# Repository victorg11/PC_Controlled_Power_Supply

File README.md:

# PC_Controlled_Power_Supply

This repository contains important information regarding the PC controlled power supply assembled in Spring 2018. This project was completed on a three month timeline with two additional team members.

Project features:
- Can supply voltages ranging 2 to 14 V.
- Capable of withstanding loads up to 1.5 A.
- Voltages and currents are adjustable via mounted buttons on encasing and USB serial connection using the standard SCPI instrumentation protocol.
- Sampled voltages and currents are displayed on an LCD touchscreen display using the SPI protocol.
- Capable of disabling outputs once maximum desired load is reached.

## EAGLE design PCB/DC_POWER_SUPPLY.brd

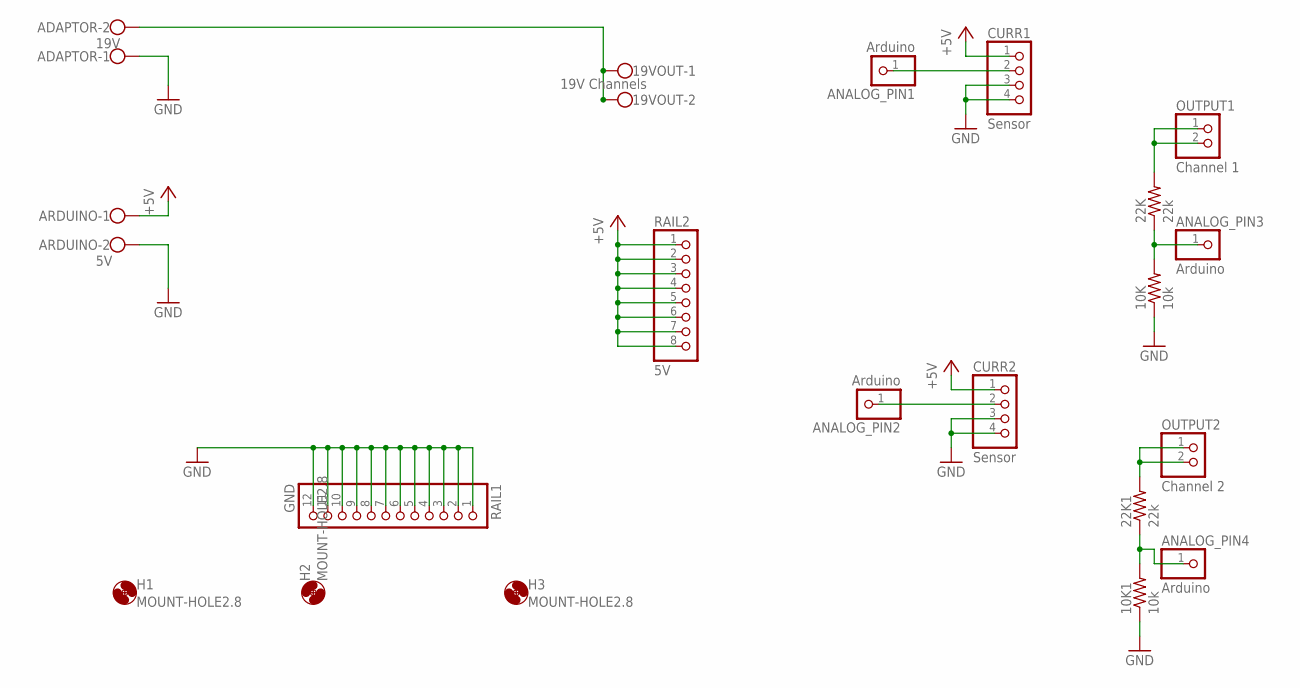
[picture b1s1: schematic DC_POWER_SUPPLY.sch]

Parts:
10K, 10K1: 10k; 0204/7
19VOUT: 19V Channels; W237-102
22K: 22k; 0207/7
22K1: 22k; 0204/7
ADAPTOR: 19V; W237-102
ANALOG_PIN1, ANALOG_PIN2, ANALOG_PIN3, ANALOG_PIN4: Arduino; 1X01
ARDUINO: 5V; W237-102
CURR1, CURR2: Sensor; 1X04
H1, H2, H3: MOUNT-HOLE2.8; 2,8
OUTPUT1: Channel 1; 1X02
OUTPUT2: Channel 2; 1X02
RAIL1: GND; 1X12
RAIL2: 5V; 1X08

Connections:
+5V: ARDUINO.1, CURR1.1, CURR2.1, RAIL2.1, RAIL2.2, RAIL2.3, RAIL2.4, RAIL2.5, RAIL2.6, RAIL2.7, RAIL2.8
GND: 10K.1, 10K1.1, ADAPTOR.1, ARDUINO.2, CURR1.3, CURR1.4, CURR2.3, CURR2.4, RAIL1.1, RAIL1.2, RAIL1.3, RAIL1.4, RAIL1.5, RAIL1.6, RAIL1.7, RAIL1.8, RAIL1.9, RAIL1.10, RAIL1.11, RAIL1.12
unnamed: 10K1.2, 22K1.1, ANALOG_PIN4.1
unnamed: ANALOG_PIN1.1, CURR1.2
unnamed: ANALOG_PIN2.1, CURR2.2
unnamed: 22K.2, OUTPUT1.1, OUTPUT1.2
unnamed: 10K.2, 22K.1, ANALOG_PIN3.1
unnamed: 22K1.2, OUTPUT2.1, OUTPUT2.2
unnamed: 19VOUT.1, 19VOUT.2, ADAPTOR.2

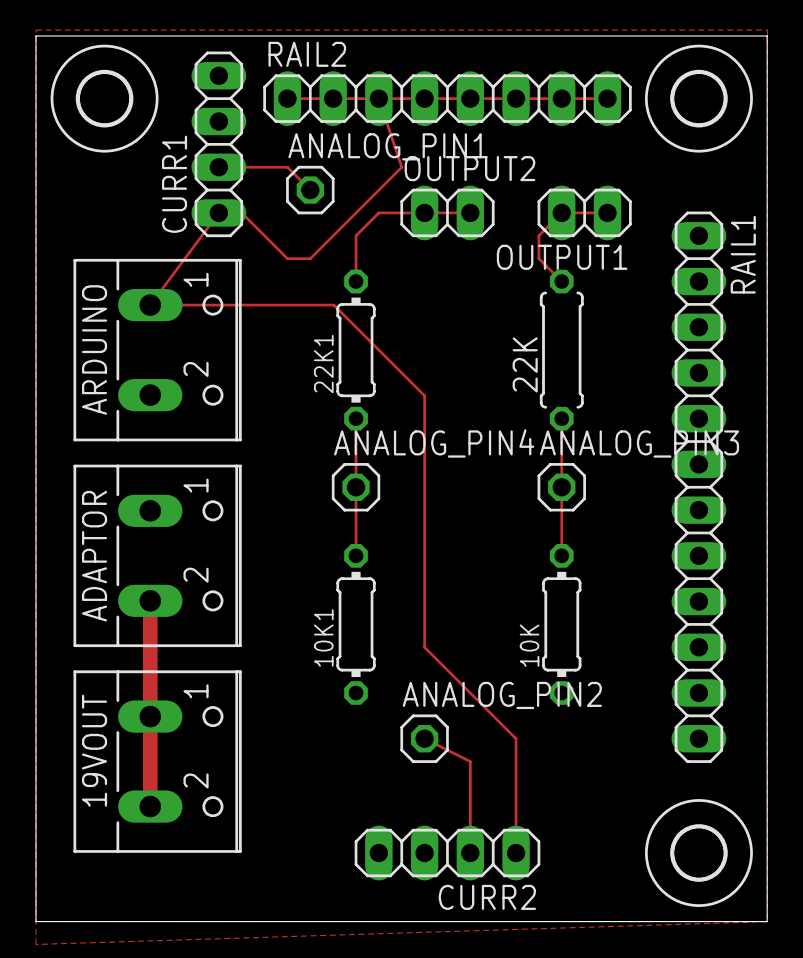
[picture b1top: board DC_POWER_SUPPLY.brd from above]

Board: 2 copper layers, 40.6 x 49.2 mm, 20 parts (0 on the bottom side), 9 nets.

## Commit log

2020-08-23 Create PCB
2020-08-23 Create temp
